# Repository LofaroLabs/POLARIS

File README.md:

# POLARIS
**Position Orientation Localization ARTag Recognition Indoor System**
*******************************************************************************
*******************************************************************************

The Position Orientation Localization ARTag Recognition Indoor System (POLARIS)
is an indoor localization module meant to provide localization functionality to
generic robots indoors. POLARIS will allow for localization through 
infrared computer vision of non-salient ARTags. When an ARTag is viewed, it 
will give the device a unique global position based on its glyph ID.

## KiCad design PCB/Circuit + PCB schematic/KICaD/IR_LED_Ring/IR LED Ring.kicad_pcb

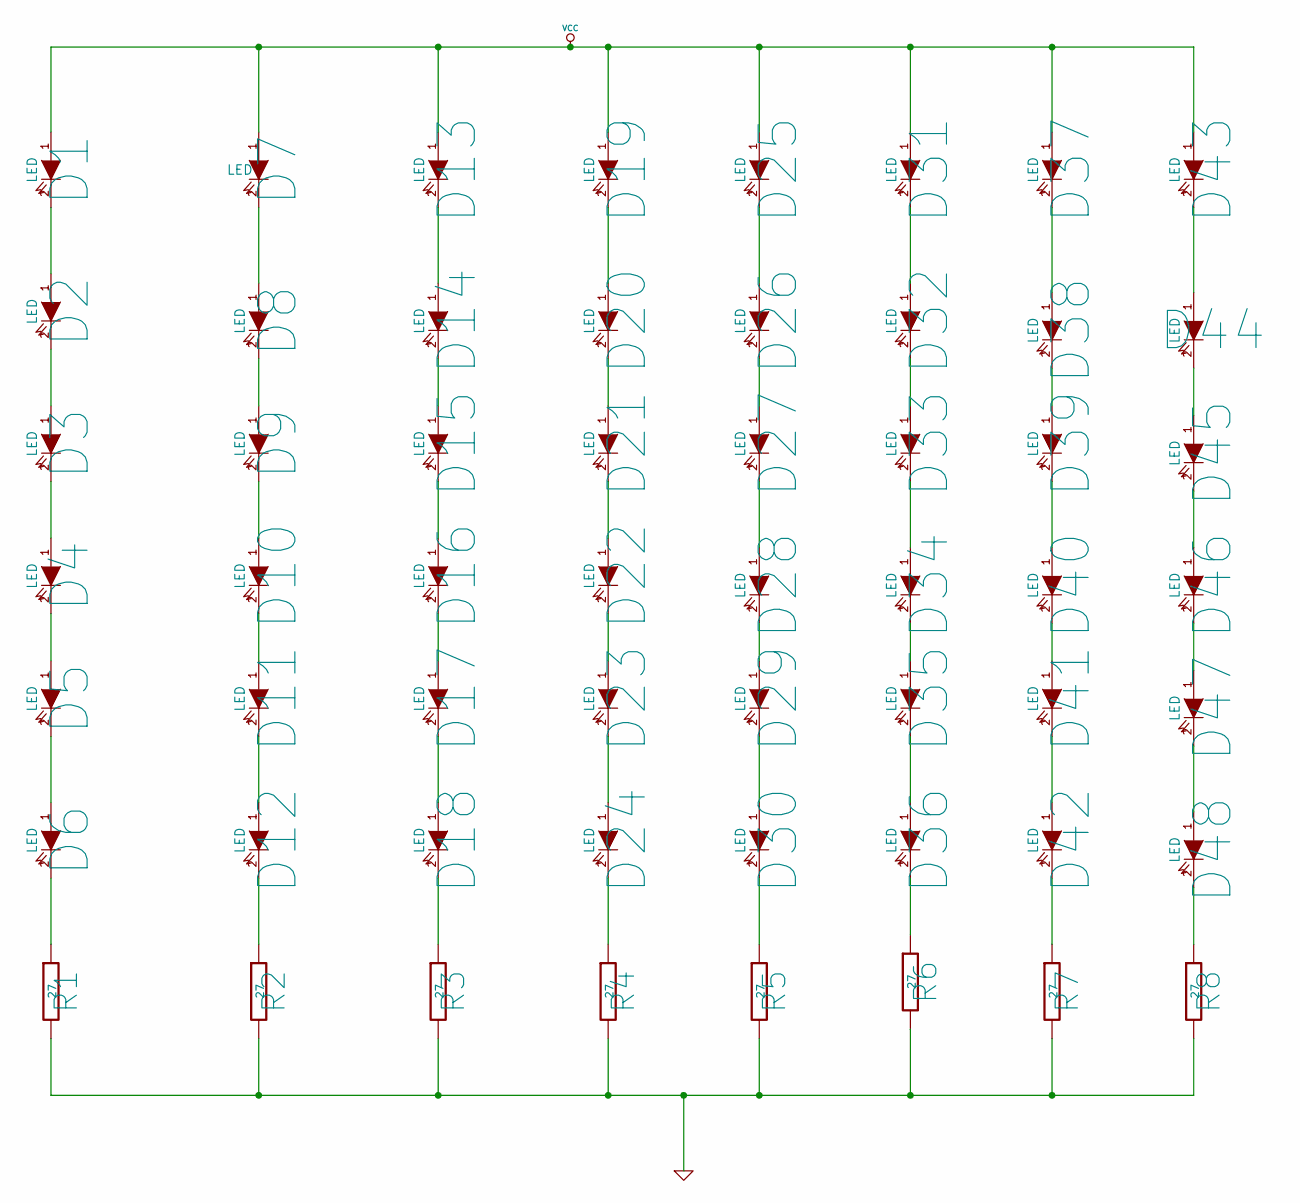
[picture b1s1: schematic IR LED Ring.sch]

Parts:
D1, D2, D3, D4, D5, D6, D7, D8, D9, D10, D11, D12, D13, D14, D15, D16, D17, D18, D19, D20, D21, D22, D23, D24, D25, D26, D27, D28, D29, D30, D31, D32, D33, D34, D35, D36, D37, D38, D39, D40, D41, D42, D43, D44, D45, D46, D47, D48: LED
R1, R2, R3, R4, R5, R6, R7, R8: 27

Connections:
GND: R1.2, R2.2, R3.2, R4.2, R5.2, R6.2, R7.2, R8.2
unnamed: D25.2 (K), D26.1 (A)
unnamed: D1.2 (K), D2.1 (A)
unnamed: D7.2 (K), D8.1 (A)
unnamed: D13.2 (K), D14.1 (A)
unnamed: D19.2 (K), D20.1 (A)
unnamed: D31.2 (K), D32.1 (A)
unnamed: D37.2 (K), D38.1 (A)
unnamed: D43.2 (K), D44.1 (A)
unnamed: D2.2 (K), D3.1 (A)
unnamed: D3.2 (K), D4.1 (A)
unnamed: D4.2 (K), D5.1 (A)
unnamed: D5.2 (K), D6.1 (A)
unnamed: D8.2 (K), D9.1 (A)
unnamed: D9.2 (K), D10.1 (A)
unnamed: D10.2 (K), D11.1 (A)
unnamed: D11.2 (K), D12.1 (A)
unnamed: D18.2 (K), R3.1
unnamed: D24.2 (K), R4.1
unnamed: D30.2 (K), R5.1
unnamed: D36.2 (K), R6.1
unnamed: D42.2 (K), R7.1
unnamed: D48.2 (K), R8.1
unnamed: D14.2 (K), D15.1 (A)
unnamed: D12.2 (K), R2.1
unnamed: D6.2 (K), R1.1
unnamed: D32.2 (K), D33.1 (A)
unnamed: D15.2 (K), D16.1 (A)
unnamed: D16.2 (K), D17.1 (A)
unnamed: D17.2 (K), D18.1 (A)
unnamed: D20.2 (K), D21.1 (A)
unnamed: D21.2 (K), D22.1 (A)
unnamed: D22.2 (K), D23.1 (A)
unnamed: D23.2 (K), D24.1 (A)
unnamed: D26.2 (K), D27.1 (A)
unnamed: D27.2 (K), D28.1 (A)
unnamed: D28.2 (K), D29.1 (A)
unnamed: D29.2 (K), D30.1 (A)
unnamed: D33.2 (K), D34.1 (A)
unnamed: D34.2 (K), D35.1 (A)
unnamed: D38.2 (K), D39.1 (A)
unnamed: D39.2 (K), D40.1 (A)
unnamed: D44.2 (K), D45.1 (A)
unnamed: D45.2 (K), D46.1 (A)
unnamed: D46.2 (K), D47.1 (A)
unnamed: D40.2 (K), D41.1 (A)
unnamed: D35.2 (K), D36.1 (A)
unnamed: D41.2 (K), D42.1 (A)
unnamed: D47.2 (K), D48.1 (A)
VCC: D1.1 (A), D7.1 (A), D13.1 (A), D19.1 (A), D25.1 (A), D31.1 (A), D37.1 (A), D43.1 (A)

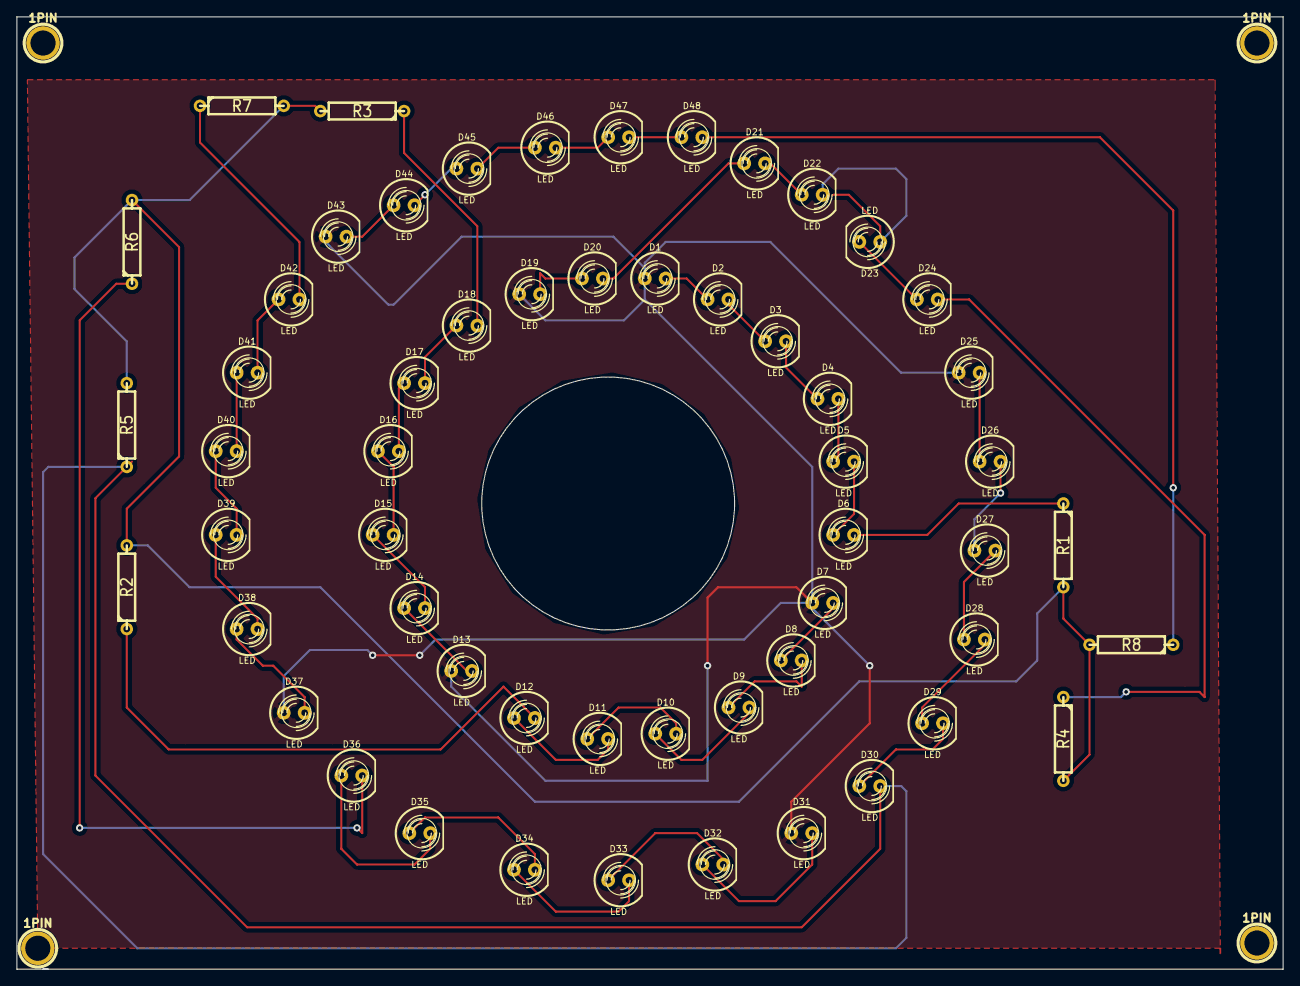
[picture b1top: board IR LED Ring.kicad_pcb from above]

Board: 2 copper layers, 153.7 x 115.6 mm, 60 parts (0 on the bottom side), 50 nets.

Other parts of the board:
1PIN, 1PIN#2, 1PIN#3, 1PIN#4: P***; 1pin

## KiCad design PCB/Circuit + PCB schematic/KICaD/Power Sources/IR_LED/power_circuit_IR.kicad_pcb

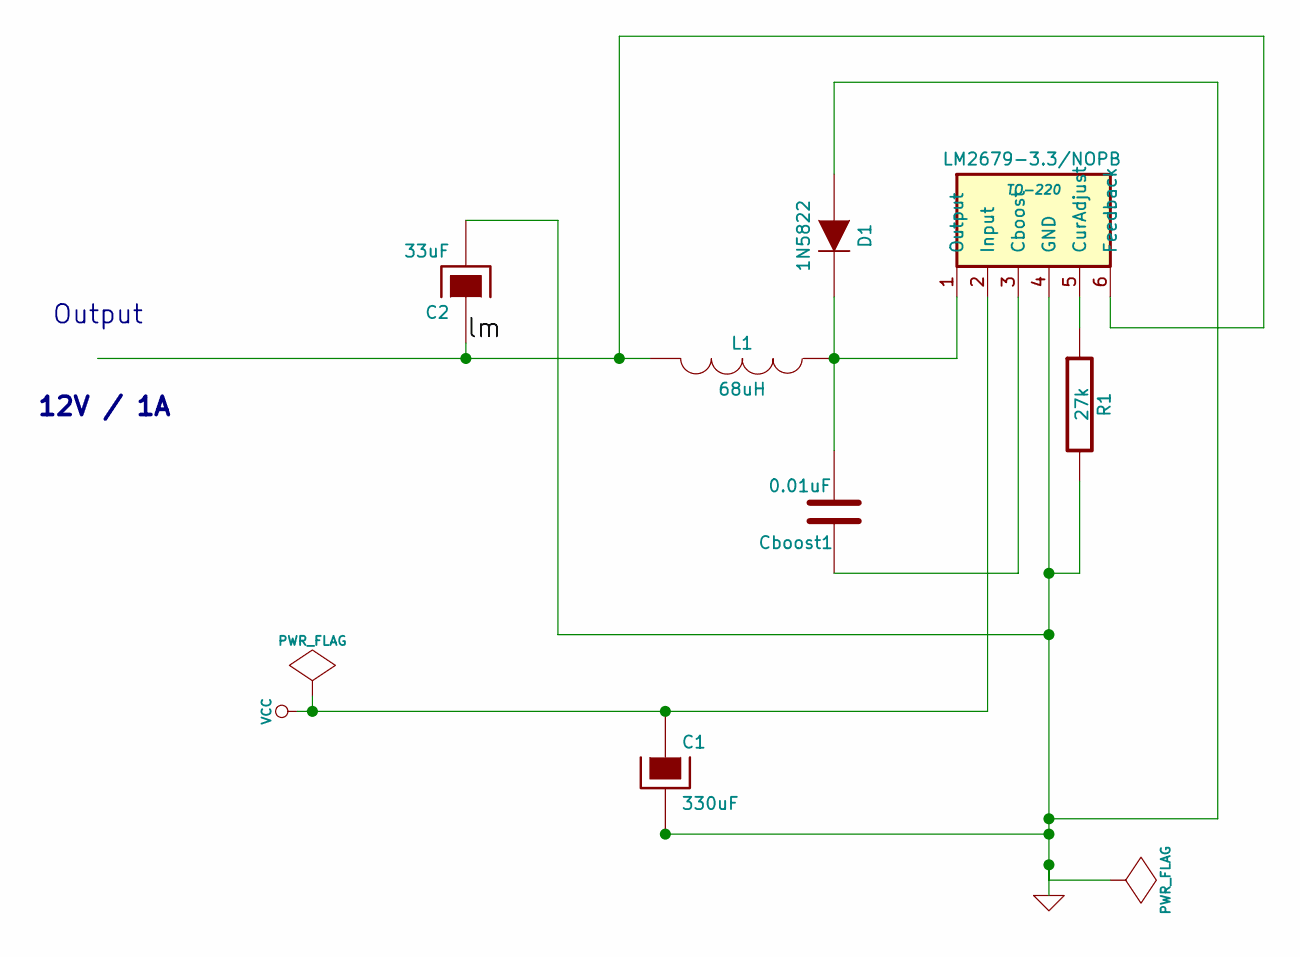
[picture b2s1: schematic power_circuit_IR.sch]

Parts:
C1: 330uF
C2: 33uF
Cboost1: 0.01uF
D1: 1N5822
L1: 68uH
R1: 27k
U1: LM2679-3.3/NOPB; TO-220

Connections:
/lm: C2.1, L1.2, U1.6 (Feedback)
GND: C1.2, C2.2, D1.1 (A), R1.2, U1.4 (GND)
unnamed: Cboost1.2, D1.2 (K), L1.1, U1.1 (Output)
unnamed: R1.1, U1.5 (CurAdjust)
unnamed: Cboost1.1, U1.3 (Cboost)
VCC: C1.1, U1.2 (Input)

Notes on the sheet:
Output
12V / 1A

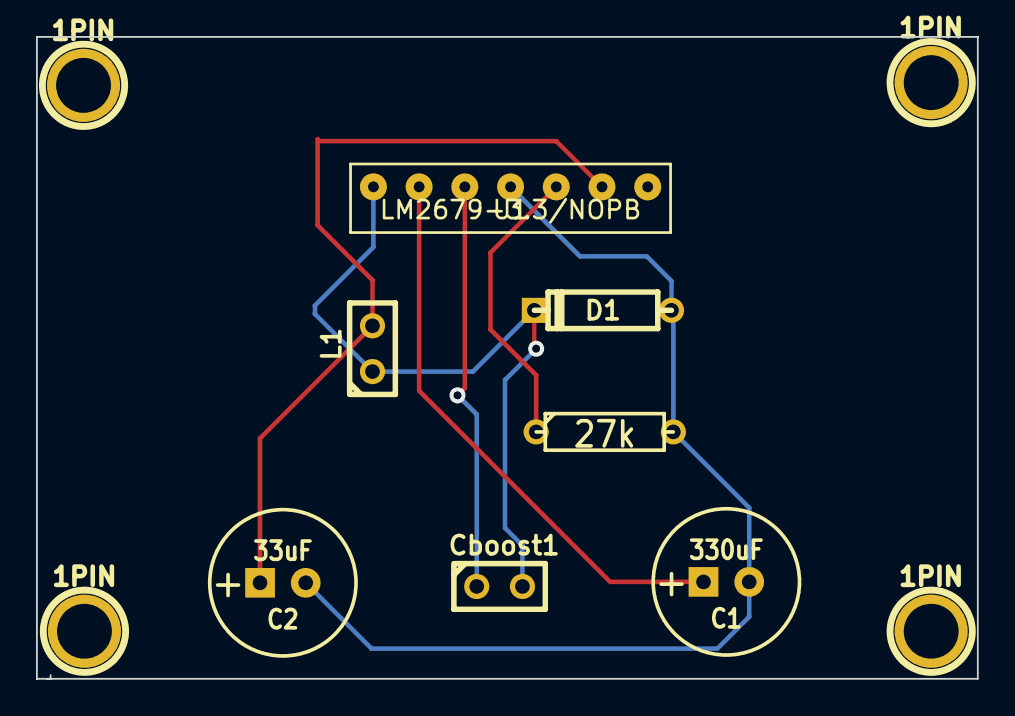
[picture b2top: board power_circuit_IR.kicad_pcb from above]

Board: 2 copper layers, 52.3 x 35.7 mm, 11 parts (0 on the bottom side), 6 nets.

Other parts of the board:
1PIN, 1PIN#2, 1PIN#3, 1PIN#4: P***; 1pin

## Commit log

2015-04-27 Inital Commit
2015-04-27 Fixed Subfolder
2015-04-27 unneed
2015-04-27 Added Serial
2015-05-12 Localization code added
2015-05-13 remove duplicated directory
2015-05-13 Adding Serial Comm
2015-05-14 Update serial comm
2015-05-18 Create PCB files
2015-05-20 SLAM assisted LUT creation partial
2015-05-22 Added PCB files
